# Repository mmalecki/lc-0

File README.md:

# Launch Controller 0

Simple switch-based model rocket launcher. When I say simple, I mean it!

Continuity checking? Yeah, sure, I'll tell you I've heard about it.

Keyed arm switch? Right, as if I had any keys laying around doing NOTHING.

I mean, frankly, the thing doesn't even have space for batteries in its enclosure.

On the other hand, its most complicated components is probably the LED telling
you the launcher is receiving power. (What, were you hoping for a switch?)

You can load a larger capacitor in there to fire a cluster of rockets with a 9 V
battery, and the 2 mm traces should withstand about anything.

## Building
First, clone this repository:
```sh
git clone https://github.com/mmalecki/lc-0
cd lc-0
git submodule update --init
```

1. Open the KiCAD project in the `electronics` directory. Get the PCB made (one-sided
is all that's needed here).
2. Render and 3D print the files in `enclosure`.

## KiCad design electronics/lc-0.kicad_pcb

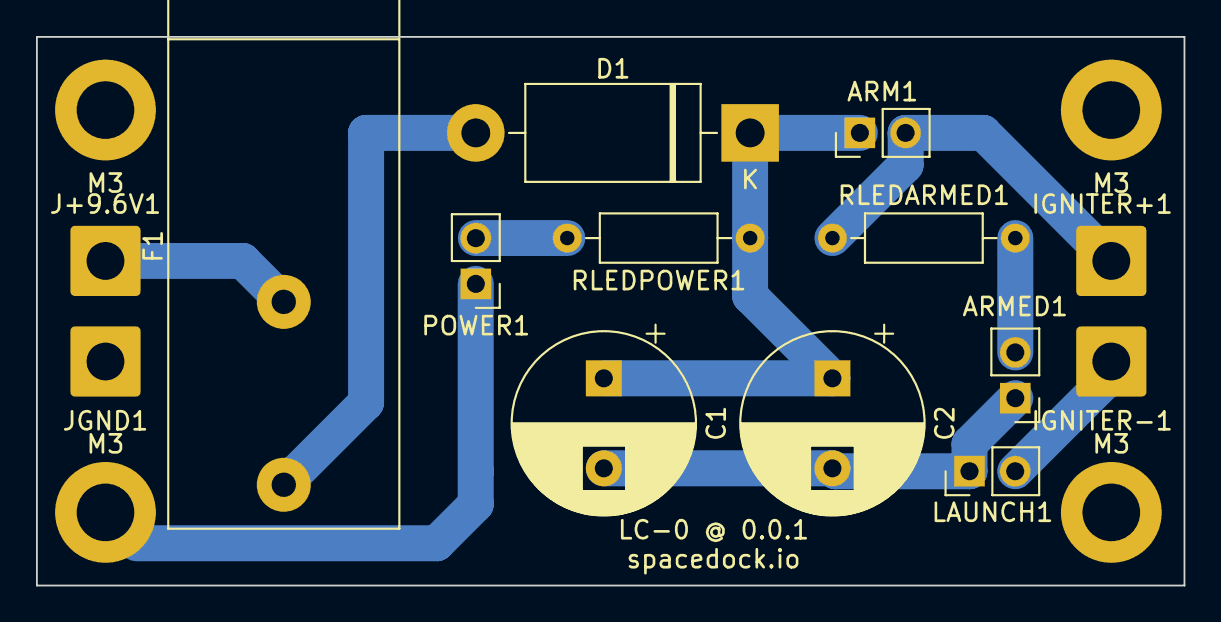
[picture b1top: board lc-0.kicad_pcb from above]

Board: 2 copper layers, 63.8 x 30.5 mm, 18 parts (0 on the bottom side), 8 nets.

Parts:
ARM1: SW_SPST; PinHeader_1x02_P2.54mm_Vertical
ARMED1: LED; PinHeader_1x02_P2.54mm_Vertical
C1, C2: 470 uF; CP_Radial_D10.0mm_P5.00mm
D1: D_Schottky; D_DO-201AD_P15.24mm_Horizontal
F1: Fuse; Fuseholder_Cylinder-5x20mm_Bulgin_FX0457_Horizontal_Closed
IGNITER+1: Conn_01x01; SolderWire-1.5sqmm_1x01_D1.7mm_OD3.9mm
IGNITER-1: Conn_01x01; SolderWire-1.5sqmm_1x01_D1.7mm_OD3.9mm
J+9.6V1: Conn_01x01; SolderWire-1.5sqmm_1x01_D1.7mm_OD3.9mm
JGND1: Conn_01x01; SolderWire-1.5sqmm_1x01_D1.7mm_OD3.9mm
LAUNCH1: SW_Push; PinHeader_1x02_P2.54mm_Vertical
M3, M3#2, M3#3, M3#4: MountingHole_3.2mm_M3_DIN965_Pad
POWER1: LED; PinHeader_1x02_P2.54mm_Vertical
RLEDARMED1: 360; R_Axial_DIN0207_L6.3mm_D2.5mm_P10.16mm_Horizontal
RLEDPOWER1: 360; R_Axial_DIN0207_L6.3mm_D2.5mm_P10.16mm_Horizontal

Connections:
GND: ARMED1.1 (K), C1.2, C2.2, JGND1.1, LAUNCH1.1, M3.1, M3#2.1, M3#3.1, M3#4.1, POWER1.1 (K)
unnamed: ARM1.1 (A), C1.1, C2.1, D1.1 (K), RLEDPOWER1.1
unnamed: ARM1.2 (B), IGNITER+1.1, RLEDARMED1.1
unnamed: ARMED1.2 (A), RLEDARMED1.2
unnamed: D1.2 (A), F1.1
unnamed: IGNITER-1.1, LAUNCH1.2
unnamed: POWER1.2 (A), RLEDPOWER1.2
VCC: F1.2, J+9.6V1.1

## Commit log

2022-01-26 .gitignore
2022-04-30 Add electronics, v0.0.1
2022-04-30 Add a README
2022-04-30 Really explain how simple this is
2022-05-01 Add enclosure dependencies
2022-05-03 Update `catchnhole`
2022-05-03 Add an enclosure
2022-05-10 Update `push-switches`
2022-05-10 Move the launch button and texts a little
2022-05-25 Add the basic build steps
2023-02-13 Add a picture of the case
2023-06-18 Minor formatting changes in the README
2023-06-22 Clean up the nutcatches
    Emboss the text instead.
2023-06-23 Let's give up on calculating the height of this
    Use M3x35's. We're short a `t`.
    This is probably the last comment here. The next one will be much more
    overengineered.
2023-06-24 Better picture
2023-06-24 Fix body height calculation
    Warning: this will likely remain untested.
